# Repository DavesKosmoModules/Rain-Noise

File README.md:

# Rain-Noise

25mm Noise Generator

- Noise generator
- White
- Pink
- Red / Brown
- Violet

Contained are schematics & gerber files for pcb fabrication of both electrical and front panel. This is sutiable for entry level however a basic level of electronics, soldering, fault finding, and some basic tools are required.

[Schematic](/Docs/Rain-Schematic.pdf)

[BOM](Docs/Rain-BOM.pdf)

To calibrate, four pots can be accessed through the holes on the front plate. 

 ` ` | ` `
 --| --
` `   | PINK      
WHITE| 
BROWN   | VIOLET

- Adjust the white pot first as this noise if filtered for the remaining sources, looking for an output of +- 5V. 
- Adjust the three remaining pots for the respective output levels. 

If you wish to edit in ki-cad the following dependencies are required

 https://github.com/holmesrichards/Kosmo_panel
 
 https://github.com/holmesrichards/aoKicad

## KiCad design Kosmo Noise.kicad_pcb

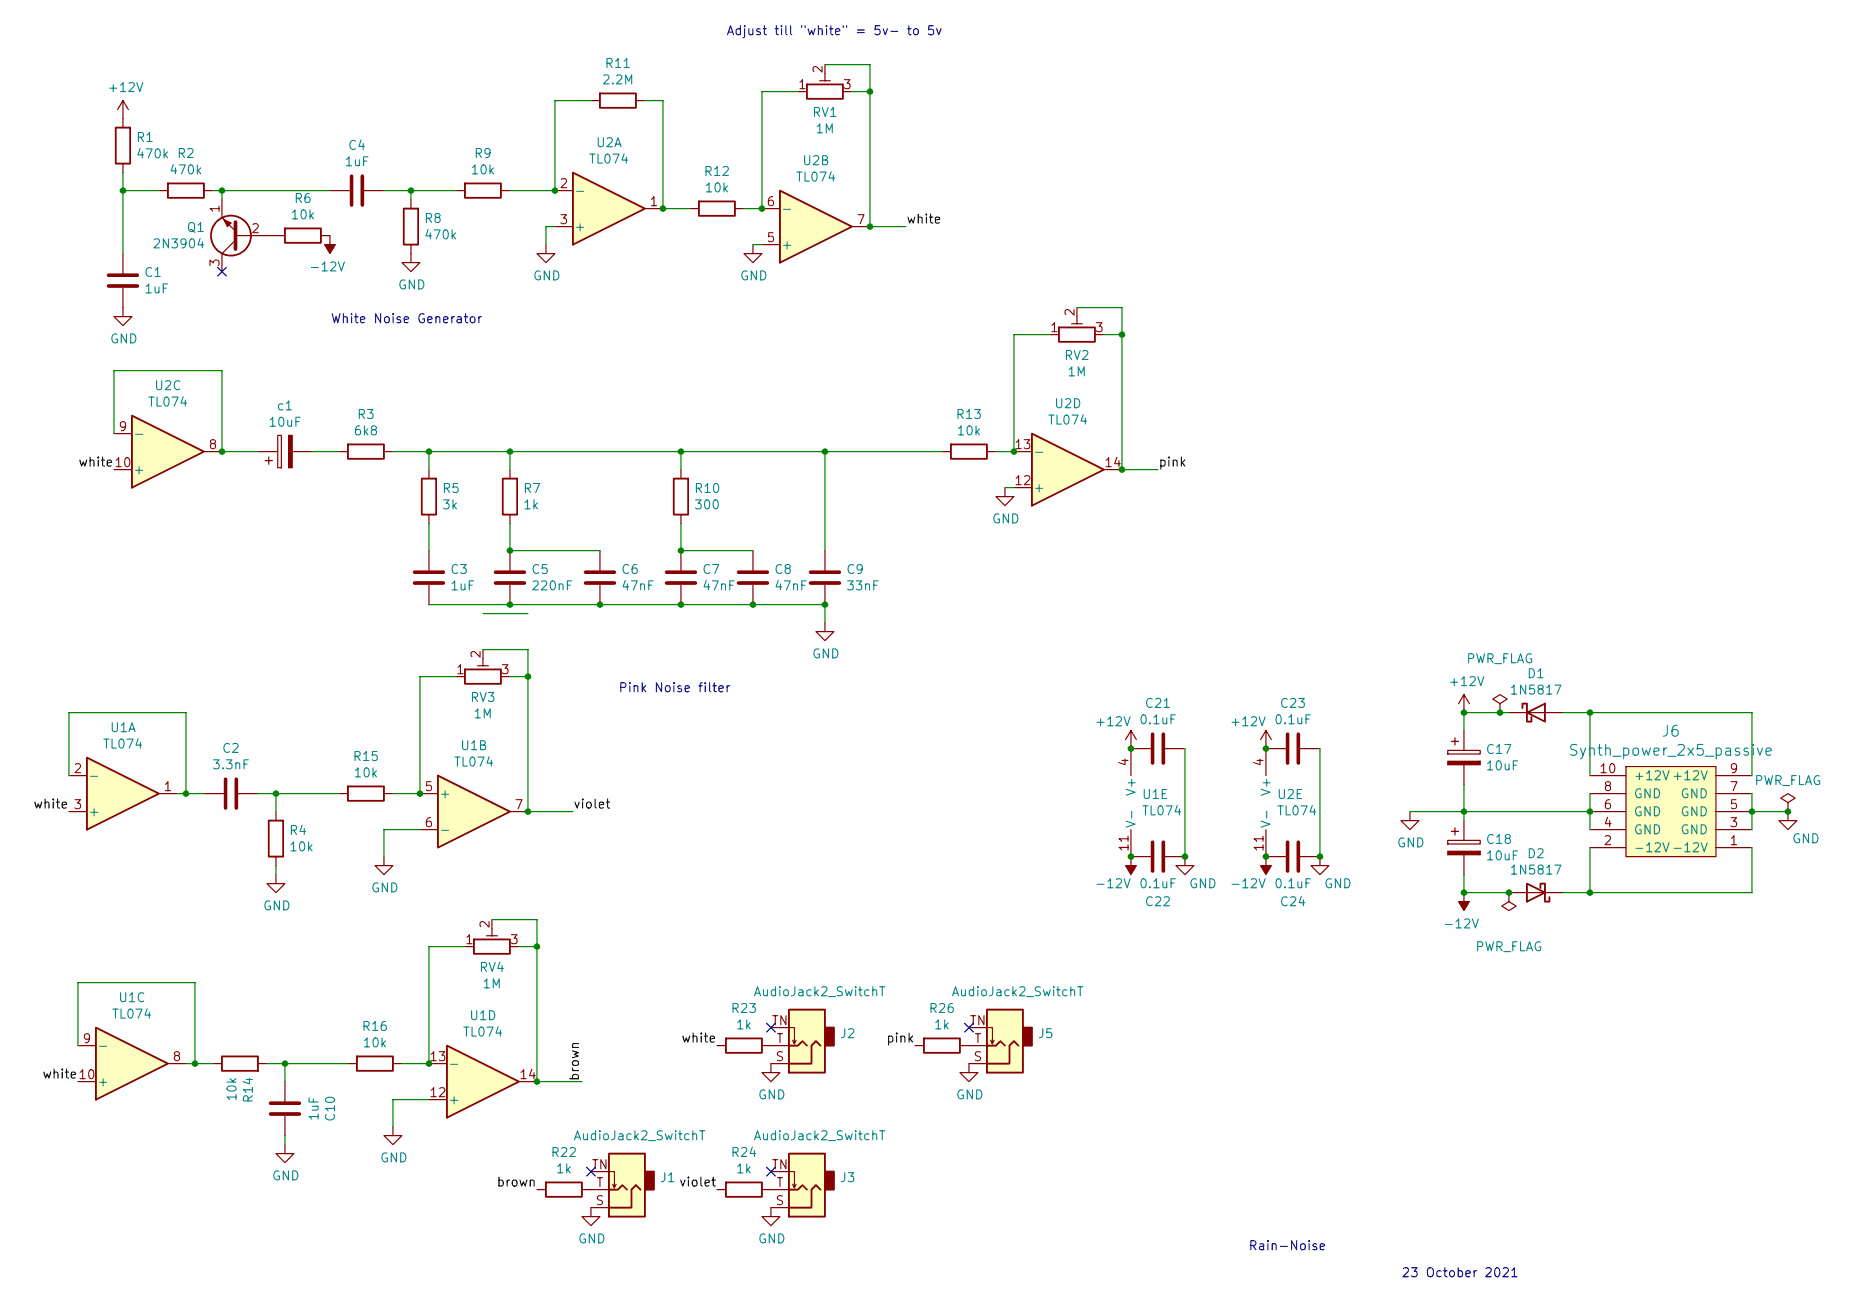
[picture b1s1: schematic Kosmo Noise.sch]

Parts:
C1, C3, C4, C10: 1uF; C_Disc_D3.0mm_W1.6mm_P2.50mm
C2: 3.3nF; C_Disc_D3.0mm_W1.6mm_P2.50mm
C5: 220nF; C_Disc_D3.0mm_W1.6mm_P2.50mm
C6, C7, C8: 47nF; C_Disc_D3.0mm_W1.6mm_P2.50mm
C9: 33nF; C_Disc_D3.0mm_W1.6mm_P2.50mm
C17, C18: 10uF; CP_Radial_D6.3mm_P2.50mm
C21, C22, C23, C24: 0.1uF; C_Disc_D3.0mm_W1.6mm_P2.50mm
D1, D2: 1N5817; D_DO-41_SOD81_P10.16mm_Horizontal
J1, J2, J3, J5: AudioJack2_SwitchT; Jack_6.35mm_PJ_629HAN
J6: Synth_power_2x5_passive; Power_Header
Q1: 2N3904; TO-92_Inline_Wide
R1, R2, R8: 470k; R_Axial_DIN0207_L6.3mm_D2.5mm_P10.16mm_Horizontal
R3: 6k8; R_Axial_DIN0207_L6.3mm_D2.5mm_P10.16mm_Horizontal
R4, R6, R9, R12, R13, R14, R15, R16: 10k; R_Axial_DIN0207_L6.3mm_D2.5mm_P10.16mm_Horizontal
R5: 3k; R_Axial_DIN0207_L6.3mm_D2.5mm_P10.16mm_Horizontal
R7, R22, R23, R24, R26: 1k; R_Axial_DIN0207_L6.3mm_D2.5mm_P10.16mm_Horizontal
R10: 300; R_Axial_DIN0207_L6.3mm_D2.5mm_P10.16mm_Horizontal
R11: 2.2M; R_Axial_DIN0207_L6.3mm_D2.5mm_P10.16mm_Horizontal
RV1, RV2, RV3, RV4: 1M; Potentiometer_Bourns_3296W_Vertical_screw_centered
U1, U2: TL074; DIP-14_W7.62mm_Socket_LongPads
c1: 10uF; CP_Radial_D6.3mm_P2.50mm

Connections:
+12V: C17.1, C21.2, C23.2, D1.1 (K), R1.2, U1.4 (V+), U2.4 (V+)
-12V: C18.2, C22.2, C24.2, D2.2 (A), R6.1, U1.11 (V-), U2.11 (V-)
/brown: R22.2, RV4.2, RV4.3, U1.14
/pink: R26.2, RV2.2, RV2.3, U2.14
/violet: R24.2, RV3.2, RV3.3, U1.7
/white: R23.2, RV1.2, RV1.3, U1.3 (+), U1.10 (+), U2.7, U2.10 (+)
GND: C1.2, C3.2, C5.2, C6.2, C7.2, C8.2, C9.2, C10.1, C17.2, C18.1, C21.1, C22.1, C23.1, C24.1, J1.S, J2.S, J3.S, J5.S, J6.3 (GND), J6.4 (GND), J6.5 (GND), J6.6 (GND), J6.7 (GND), J6.8 (GND), R4.1, R8.1, U1.6 (-), U1.12 (+), U2.3 (+), U2.5 (+), U2.12 (+)
unnamed: C1.1, R1.1, R2.2
unnamed: C2.1, R4.2, R15.2
unnamed: C2.2, U1.1, U1.2 (-)
unnamed: C3.1, R5.1
unnamed: C4.1, Q1.1 (E), R2.1
unnamed: C4.2, R8.2, R9.2
unnamed: C5.1, C6.1, R7.1
unnamed: C7.1, C8.1, R10.1
unnamed: C9.1, R3.1, R5.2, R7.2, R10.2, R13.2
unnamed: C10.2, R14.2, R16.2
unnamed: D1.2 (A), J6.9 (+12V), J6.10 (+12V)
unnamed: D2.1 (K), J6.1 (-12V), J6.2 (-12V)
unnamed: J1.T, R22.1
unnamed: J2.T, R23.1
unnamed: J3.T, R24.1
unnamed: J5.T, R26.1
unnamed: Q1.2 (B), R6.2
unnamed: R3.2, c1.2
unnamed: R11.1, R12.2, U2.1
unnamed: R9.1, R11.2, U2.2 (-)
unnamed: R12.1, RV1.1, U2.6 (-)
unnamed: R13.1, RV2.1, U2.13 (-)
unnamed: R14.1, U1.8, U1.9 (-)
unnamed: R15.1, RV3.1, U1.5 (+)
unnamed: R16.1, RV4.1, U1.13 (-)
unnamed: U2.8, U2.9 (-), c1.1

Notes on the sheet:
Adjust till "white" = 5v- to 5v
White Noise Generator
Pink Noise filter
Rain-Noise
23 October 2021

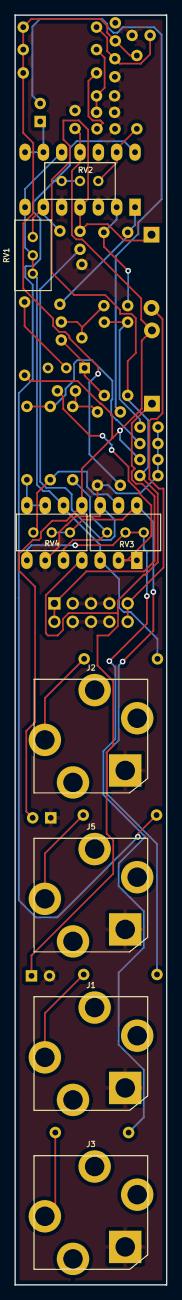
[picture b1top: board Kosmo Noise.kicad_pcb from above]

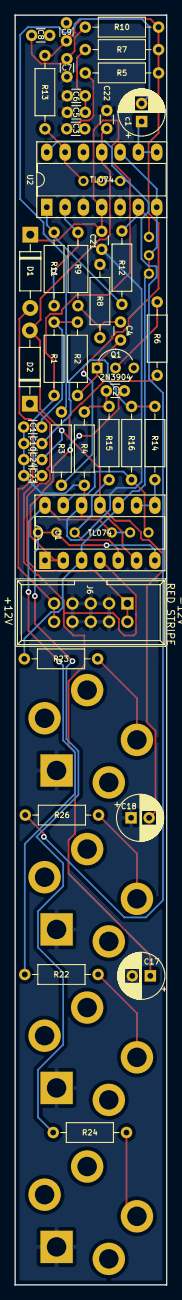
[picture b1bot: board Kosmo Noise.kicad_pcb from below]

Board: 2 copper layers, 21.0 x 176.0 mm, 51 parts (43 on the bottom side), 33 nets.

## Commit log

2021-10-23 Initial
2021-10-30 Calibration added to readme
